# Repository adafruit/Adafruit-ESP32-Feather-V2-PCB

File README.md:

## Adafruit ESP32 Feather V2 PCB

<a href="http://www.adafruit.com/products/5400"><br/>
Click here to purchase one from the Adafruit shop</a>

PCB files for the Adafruit ESP32 Feather V2. 

Format is EagleCAD schematic and board layout
* https://www.adafruit.com/product/5400

### Description

One of our star Feathers is the Adafruit HUZZAH32 ESP32 Feather - with the fabulous ESP32 WROOM module on there, it makes quick work of WiFi and Bluetooth projects that take advantage of Espressifs most popular chipset. Recently we had to redesign this feather to move from the obsolete CP2104 to the CP2012N and one thing led to another and before you know it we made a completely refreshed design: the Adafruit ESP32 Feather V2.

The V2 is a significant redesign, enough so we consider it a completely new product. It still features the ESP32 chip but has many upgrades and improvements:

* Compared to the original Feather with 4 MB Flash and no PSRAM, the V2 has 8 MB Flash and 2 MB PSRAM
* Additional user button tactile switch on input pin 38
* Additional NeoPixel mini RGB LED with controllable power pin
* Additional STEMMA QT port for plug and play I2C connections
* USB Type C port instead of Micro B
* Separate controllable 3.3V power supply for STEMMA QT to allow for ultra low power consumption even with sensors are attached
* Designed for low power usage: verified with a PPK to draw 70uA from the Lipoly battery in deep sleep and 1.2mA in light sleep.
* ESP32 Pico module is much smaller, allowing for clear marking of all breakout pads and additional mounting holes!
* Upgrade the USB to serial converter from CP2014 (2mbps max rate) to CP2102N which can handle 3 mbps

However, in order to add the PSRAM, and use the new Pico module which was small enough to allow all the fun extras, some of the breakout pads have changed, so here's what you need to know:

* The pin numbers for the I2C port (SDA, SCL), hardware UART (RX, TX), and SPI (SCK, MOSI, MISO) have changed. If your code has hardcoded use for those pins, you'll want to replace them either by the new numbers or change the code to use the 'pretty' names like SDA or SCK.
* When selecting the new Feather ESP32 V2 board in the Espressif board support package, the correct numbers will be substituted.
* Note the names are in the same spots, we haven't changed where the I2C/UART/SPI pins are located on the board, just which ESP32 pin numbers they are connected to in the module.
* The 'corner' pin next to TX has changed from pin 21 to 37. This pin is not used in any FeatherWings because its considered an 'extra pin'. It's also changed from a GPIO to input-only
* The remaining numbered pins and A0-A5 pins have not changed pin numbers.

That module nestled in at the end of this Feather contains a dual-core ESP32 chip, 8 MB of SPI Flash, 2 MB of PSRAM, tuned PCB antenna, and all the passives you need to take advantage of this powerful new processor. The ESP32 has both WiFi and Bluetooth Classic/LE support. That means it's perfect for just about any wireless or Internet-connected project.

Because it's part of our Feather eco-system, you can take advantage of the 50+ Wings that we've designed to add all sorts of cool accessories. Plus that built in battery charging and monitoring you know and love with the ESP32 Feather is still there in this upgrade.

Features:

* ESP32 Dual core 240MHz Xtensa® processor - the classic dual-core ESP32 you know and love!
* Mini module has FCC/CE certification and comes with 8 MByte of Flash and 2 MByte of PSRAM - you can have huge data buffers
* Power options - USB type C or Lipoly battery
* Built-in battery charging when powered over USB-C
* LiPoly battery monitor with two 200K resistor divider
* Reset and User (I38) buttons to reset board and as a separate input
* High speed upload with auto-reset and serial debug with ultra-reliable CP2102N chipset.
* STEMMA QT connector for I2C devices, with switchable power, so you can go into low power mode.
* Charge/User LEDs + status NeoPixel with pin-controlled power for low power usage
* Low Power friendly! In deep sleep mode we can get down to 80~100uA of current draw from the Lipoly connection. Quiescent current is from the power regulator, ESP32 chip, and Lipoly monitor. Turn off the NeoPixel and external I2C power for the lowest quiescent current draw.
* Works with Arduino or MicroPython

Comes fully assembled and tested, with a USB interface that lets you quickly use it with the Arduino IDE or the low-level ESP32 IDF. We also toss in some header so you can solder it in and plug into a solderless breadboard. Lipoly battery and USB cable not included (but we do have lots of options in the shop if you'd like!)

### License

Adafruit invests time and resources providing this open source design, please support Adafruit and open-source hardware by purchasing products from [Adafruit](https://www.adafruit.com)!

Designed by Limor Fried/Ladyada for Adafruit Industries.

Creative Commons Attribution/Share-Alike, all text above must be included in any redistribution. 
See license.txt for additional details.

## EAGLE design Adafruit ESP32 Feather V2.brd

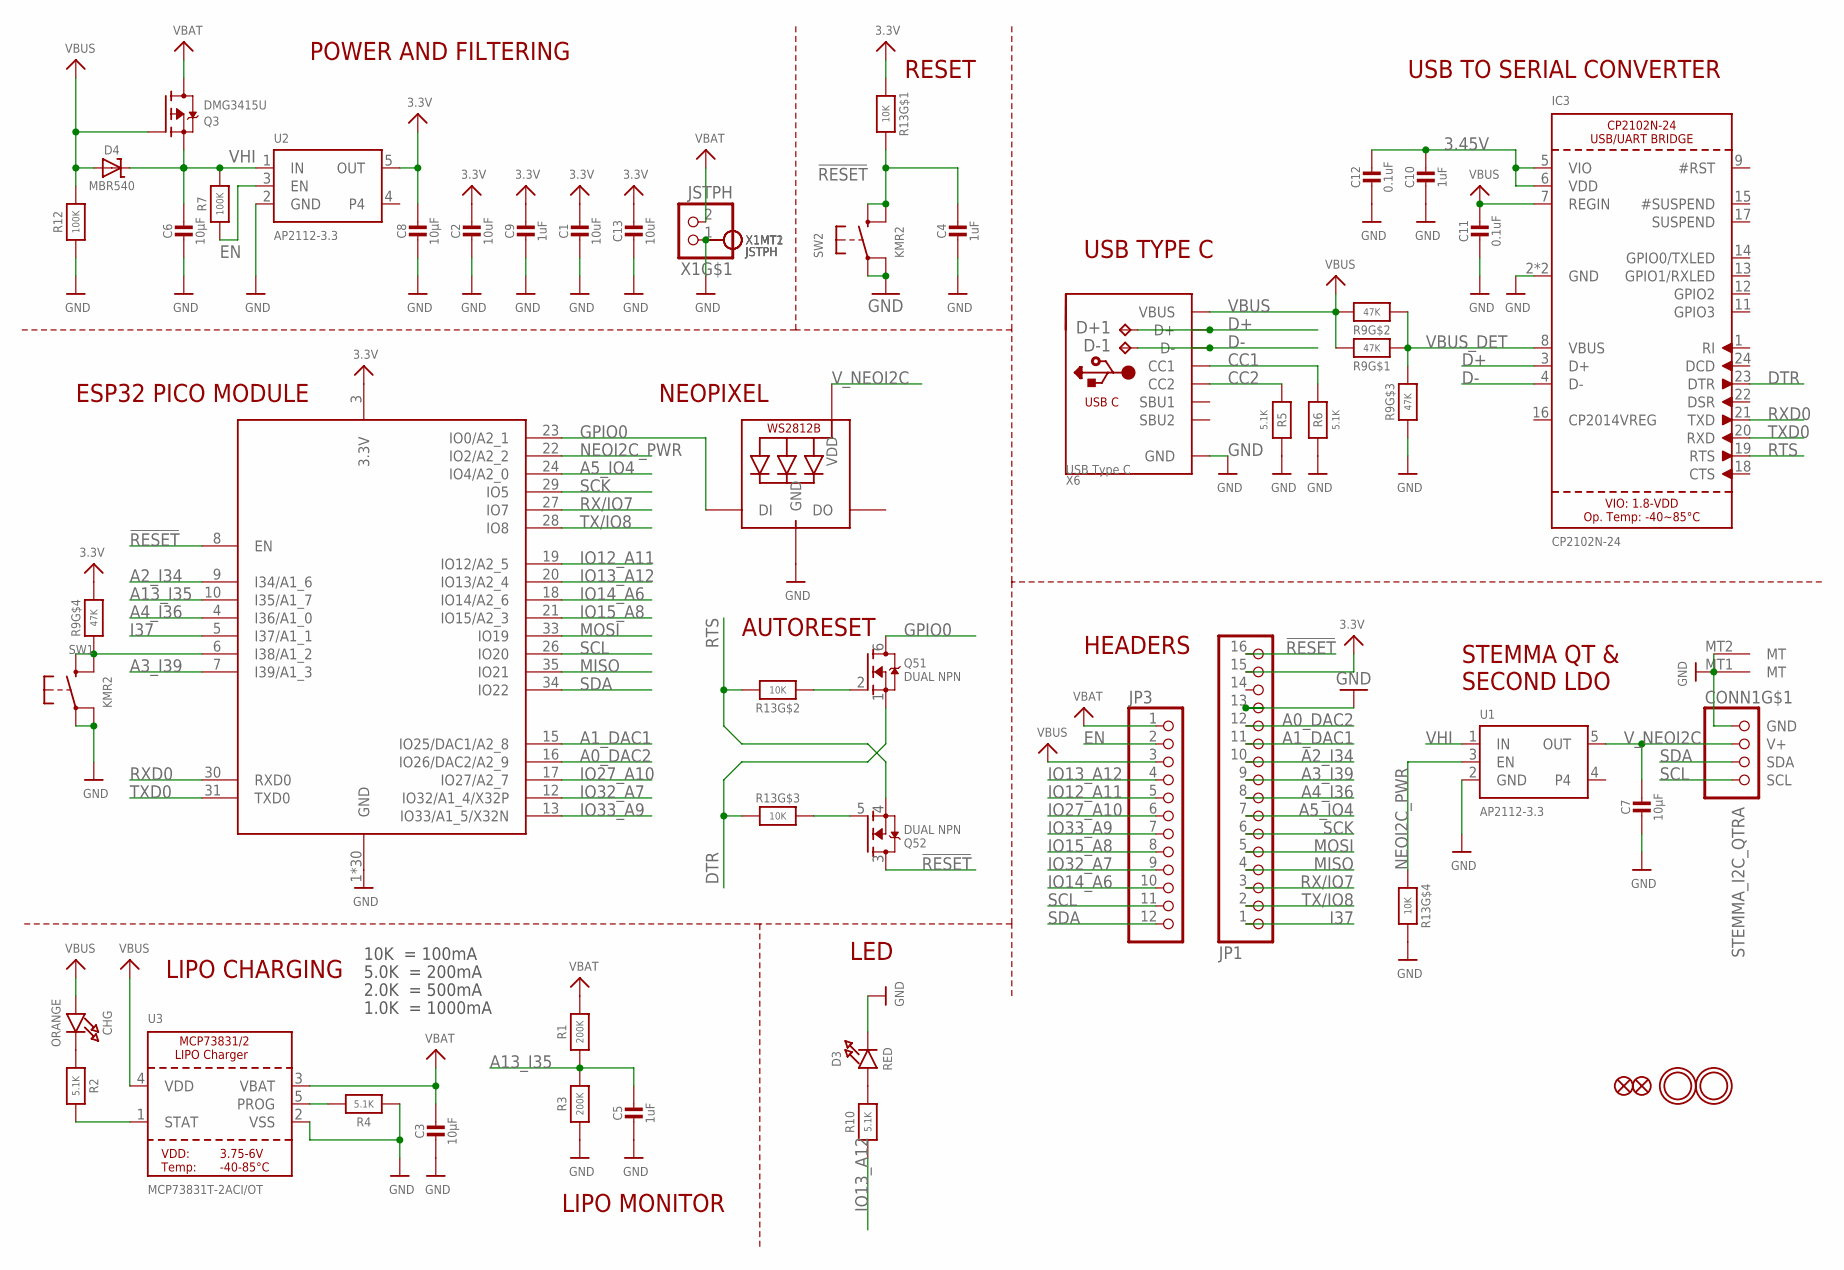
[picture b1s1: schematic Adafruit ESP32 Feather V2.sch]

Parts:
C1, C2, C13: 10uF; 0805-NO
C3, C6, C7, C8: 10µF; 0805-NO
C4, C5, C9, C10: 1uF; 0603-NO
C11, C12: 0.1uF; 0603-NO
CHG: ORANGE; CHIPLED_0603_NOOUTLINE
CONN1: STEMMA_I2C_QTRA; JST_SH4_RA
D3: RED; CHIPLED_0603_NOOUTLINE
D4: MBR540; SOD-123
D+1: TPB1,27; B1,27
D-1: TPB1,27; B1,27
IC3: CP2102N-24; QFN24_4MM_SMSC
JP1: HEADER-1X16ROUND; 1X16_ROUND
JP3: HEADER-1X12; 1X12_ROUND
LED1: WS2812B3535; LED3535
Q3: DMG3415U; SOT23-R
Q5: DUAL NPN; SOT363
R1, R3: 200K; 0603-NO
R2, R4, R5, R6, R10: 5.1K; 0603-NO
R7, R12: 100K; 0603-NO
R9: 47K; RESPACK_4X0603
R13: 10K; RESPACK_4X0603
SW1, SW2: KMR2; BTN_KMR2_4.6X2.8
U1, U2: AP2112-3.3; SOT23-5
U3: MCP73831T-2ACI/OT; SOT23-5
U$31, U$32: MOUNTINGHOLE2.5; MOUNTINGHOLE_2.5_PLATED
U$34, U$35: FIDUCIAL_1MM
X1: JSTPH; JSTPH2_BATT
X3: ESP32-PICO-MINI-02MINI; ESP32-PICO-MINI
X6: USB Type C; USB_C_CUSB31-CFM2AX-01-X

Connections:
3.3V: C1.1, C2.1, C8.1, C9.1, C13.1, JP1.15, R9.5 (2), R13.1, U2.5 (OUT), X3.3 (3.3V)
3.45V: C10.1, C12.1, IC3.5 (VIO), IC3.6 (VDD)
!RESET: C4.1, JP1.16, Q5.3 (D), R13.8 (2), SW2.B (S), SW2.B' (S1), X3.8 (EN)
A0_DAC2: JP1.12, X3.16 (IO26/DAC2/A2_9)
A1_DAC1: JP1.11, X3.15 (IO25/DAC1/A2_8)
A2_I34: JP1.10, X3.9 (I34/A1_6)
A3_I39: JP1.9, X3.7 (I39/A1_3)
A4_I36: JP1.8, X3.4 (I36/A1_0)
A5_IO4: JP1.7, X3.24 (IO4/A2_0)
A13_I35: C5.1, R1.1, R3.2, X3.10 (I35/A1_7)
CC1: R6.2, X6.A5 (CC1)
CC2: R5.2, X6.B5 (CC2)
D+: D+1.TP, IC3.3 (D+), X6.A6 (D+), X6.B6 (D+)
D-: D-1.TP, IC3.4 (D-), X6.A7 (D-), X6.B7 (D-)
DTR: IC3.23 (DTR), Q5.1 (S), R13.3 (1)
EN: JP3.2, R7.1, U2.3 (EN)
GND: C1.2, C2.2, C3.2, C4.2, C5.2, C6.2, C7.2, C8.2, C9.2, C10.2, C11.2, C12.2, C13.2, CONN1.1 (GND), CONN1.MT1 (MT), CONN1.MT2 (MT), D3.C, IC3.2 (GND), IC3.THERM (GND), JP1.13, LED1.4 (GND), R3.1, R4.1, R5.1, R6.1, R9.3 (1), R12.1, R13.5 (2), SW1.A, SW1.A' (P1), SW2.A, SW2.A' (P1), U1.2 (GND), U2.2 (GND), U3.2 (VSS), X1.1, X1.NC1, X1.NC2, X3.1 (GND), X3.2 (GND), X3.11 (GND), X3.14 (GND), X3.36 (GND), X3.37 (GND), X3.38 (GND), X3.39 (GND), X3.40 (GND), X3.41 (GND), X3.42 (GND), X3.43 (GND), X3.44 (GND), X3.45 (GND), X3.46 (GND), X3.47 (GND), X3.48 (GND), X3.49 (GND), X3.50 (GND), X3.51 (GND), X3.52 (GND), X3.53 (GND), X3.54 (GND), X3.55 (GND), X3.56 (GND), X3.57 (GND), X3.58 (GND), X3.59 (GND), X3.60 (GND), X3.61 (GND), X6.A1B12 (GND), X6.B1A12 (GND)
GPIO0: LED1.1 (DI), Q5.6 (D), X3.23 (IO0/A2_1)
I37: JP1.1, X3.5 (I37/A1_1)
IO12_A11: JP3.5, X3.19 (IO12/A2_5)
IO13_A12: JP3.4, R10.1, X3.20 (IO13/A2_4)
IO14_A6: JP3.10, X3.18 (IO14/A2_6)
IO15_A8: JP3.8, X3.21 (IO15/A2_3)
IO27_A10: JP3.6, X3.17 (IO27/A2_7)
IO32_A7: JP3.9, X3.12 (IO32/A1_4/X32P)
IO33_A9: JP3.7, X3.13 (IO33/A1_5/X32N)
MISO: JP1.4, X3.35 (IO21)
MOSI: JP1.5, X3.33 (IO19)
unnamed: CHG.C, R2.1
unnamed: R2.2, U3.1 (STAT)
unnamed: R4.2, U3.5 (PROG)
unnamed: D3.A, R10.2
unnamed: R9.4 (1), SW1.B (S), SW1.B' (S1), X3.6 (I38/A1_2)
unnamed: Q5.5 (G), R13.6 (2)
unnamed: Q5.2 (G), R13.2 (1)
NEOI2C_PWR: R13.4 (1), U1.3 (EN), X3.22 (IO2/A2_2)
RTS: IC3.19 (RTS), Q5.4 (S), R13.7 (2)
RX/IO7: JP1.3, X3.27 (IO7)
RXD0: IC3.21 (TXD), X3.30 (RXD0)
SCK: JP1.6, X3.29 (IO5)
SCL: CONN1.4 (SCL), JP3.11, X3.26 (IO20)
SDA: CONN1.3 (SDA), JP3.12, X3.34 (IO22)
TX/IO8: JP1.2, X3.28 (IO8)
TXD0: IC3.20 (RXD), X3.31 (TXD0)
VBAT: C3.1, JP3.1, Q3.3 (D), R1.2, U3.3 (VBAT), X1.2
VBUS: C11.1, CHG.A, D4.A, IC3.7 (REGIN), JP3.3, Q3.1 (G), R9.7 (2), R9.8 (2), R12.2, U3.4 (VDD), X6.A4B9 (VBUS), X6.B4A9 (VBUS)
VBUS_DET: IC3.8 (VBUS), R9.1, R9.2 (1), R9.6 (2)
VHI: C6.1, D4.C, Q3.2 (S), R7.2, U1.1 (IN), U2.1 (IN)
V_NEOI2C: C7.1, CONN1.2 (V+), LED1.2 (VDD), U1.5 (OUT)

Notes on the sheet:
POWER AND FILTERING
RESET
10K = 100mA
5.0K = 200mA
2.0K = 500mA
1.0K = 1000mA
USB TO SERIAL CONVERTER
LIPO CHARGING
LED
ESP32 PICO MODULE
LIPO MONITOR
HEADERS
STEMMA QT & SECOND LDO
USB TYPE C
AUTORESET
NEOPIXEL

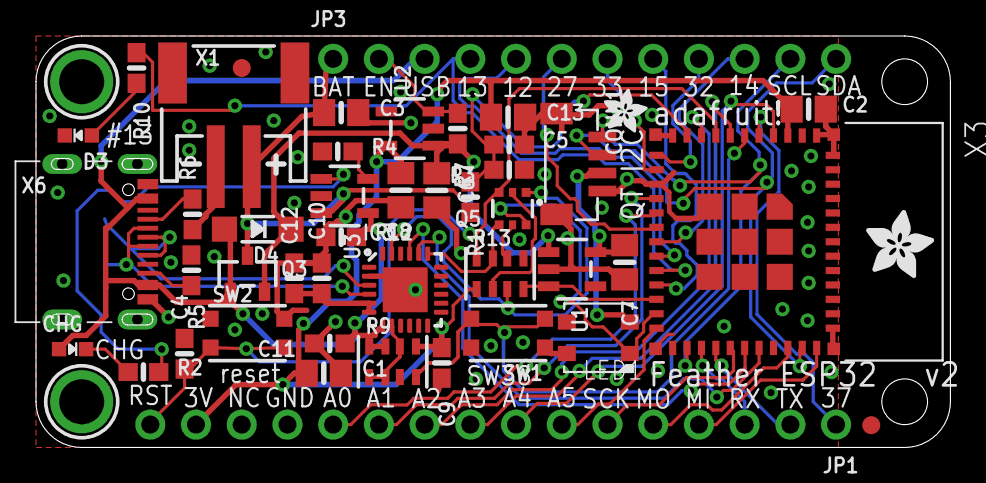
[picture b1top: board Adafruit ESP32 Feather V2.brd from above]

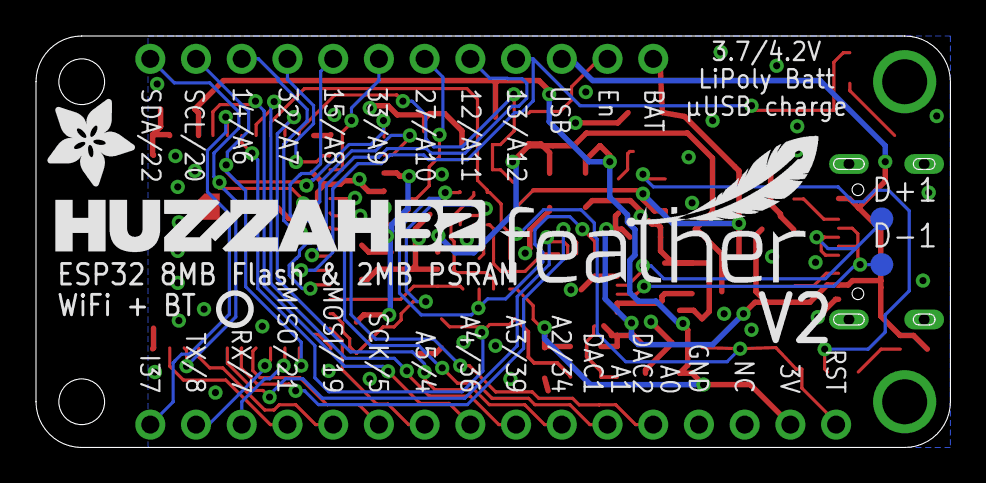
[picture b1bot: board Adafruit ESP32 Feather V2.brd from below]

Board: 2 copper layers, 50.8 x 22.9 mm, 54 parts (6 on the bottom side), 49 nets.

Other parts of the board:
U$7: ADAFRUIT_5MM
U$9: FEATHERLOGO_MED
U$13: PCBFEAT-REV-040
U$14: ADAFRUIT_2.5MM
U$15: ADAFRUIT_3.5MM
U$43: HUZZAH32

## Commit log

2022-03-08 Add initial files.
2022-03-09 Add PrettyPins.
2022-03-09 Add factory reset file.
2022-06-27 Updated PrettyPins PDF
2022-07-05 Uploaded fixed prettypins
2023-08-10 Remove for updated version.
2023-08-10 Now with CircuitPython!

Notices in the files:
parts and their libraries:
microbuilder: This work is placed in the public domain, and may be freely used for commercial and non-commercial work with the following conditions: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
